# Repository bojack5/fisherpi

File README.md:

# FisherPi
Python code for controlling robo TX Automation Robots via raspberry pi

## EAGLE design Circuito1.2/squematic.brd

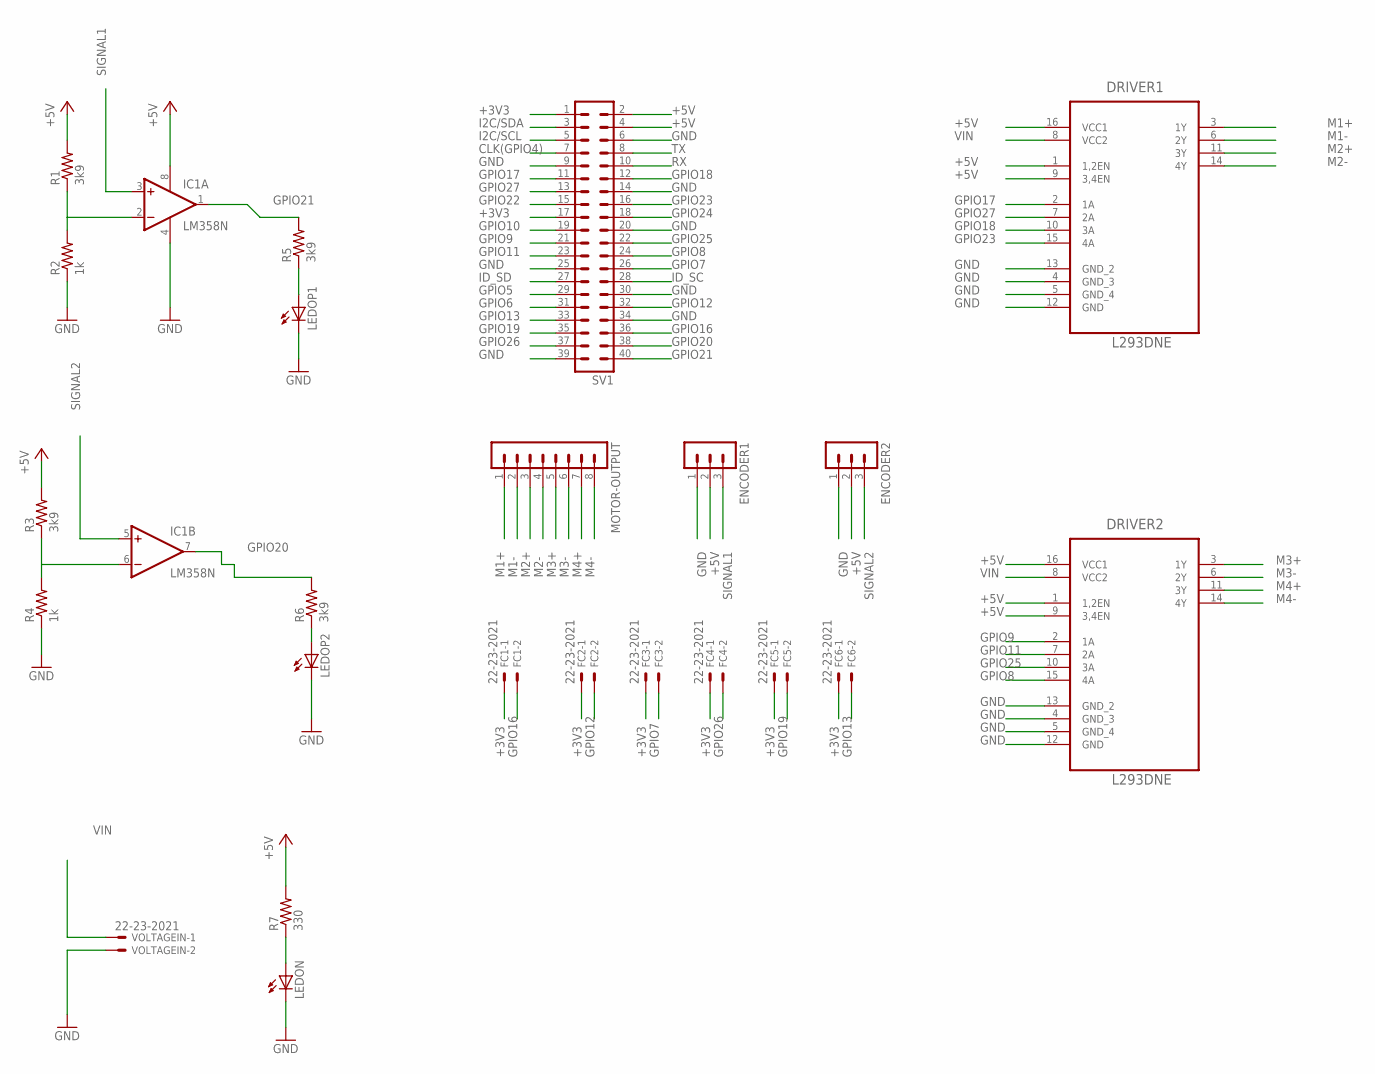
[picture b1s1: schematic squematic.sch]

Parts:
DRIVER1, DRIVER2: L293DNE; DIP254P762X508-16
ENCODER1, ENCODER2: MA03-1
FC1, FC2, FC3, FC4, FC5, FC6: 22-23-2021
IC1: LM358N; DIL08
LEDON: LED_ELD260; LED_LD260
LEDOP1, LEDOP2: LED_ELD260; LED_LD260
MOTOR-OUTPUT: MA08-1
R1, R3, R5, R6: 3k9; 0207/10
R2, R4: 1k; 0207/10
R7: 330; 0207/10
SV1: MA20-2
VOLTAGEIN: 22-23-2021

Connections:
+3V3: FC1.1, FC2.1, FC3.1, FC4.1, FC5.1, FC6.1, SV1.1, SV1.17
+5V: DRIVER1.1 (1,2EN), DRIVER1.9 (3,4EN), DRIVER1.16 (VCC1), DRIVER2.1 (1,2EN), DRIVER2.9 (3,4EN), DRIVER2.16 (VCC1), ENCODER1.2, ENCODER2.2, IC1.8 (V+), R1.2, R3.2, R7.2, SV1.2, SV1.4
CLK(GPIO4): SV1.7
GND: DRIVER1.4 (GND_3), DRIVER1.5 (GND_4), DRIVER1.12 (GND), DRIVER1.13 (GND_2), DRIVER2.4 (GND_3), DRIVER2.5 (GND_4), DRIVER2.12 (GND), DRIVER2.13 (GND_2), ENCODER1.1, ENCODER2.1, IC1.4 (V-), LEDON.K (C), LEDOP1.K (C), LEDOP2.K (C), R2.1, R4.1, SV1.6, SV1.9, SV1.14, SV1.20, SV1.25, SV1.30, SV1.34, SV1.39, VOLTAGEIN.2
GPIO5: SV1.29
GPIO6: SV1.31
GPIO7: FC3.2, SV1.26
GPIO8: DRIVER2.15 (4A), SV1.24
GPIO9: DRIVER2.2 (1A), SV1.21
GPIO10: SV1.19
GPIO11: DRIVER2.7 (2A), SV1.23
GPIO12: FC2.2, SV1.32
GPIO13: FC6.2, SV1.33
GPIO16: FC1.2, SV1.36
GPIO17: DRIVER1.2 (1A), SV1.11
GPIO18: DRIVER1.10 (3A), SV1.12
GPIO19: FC5.2, SV1.35
GPIO20: IC1.7 (OUT), R6.2, SV1.38
GPIO21: IC1.1 (OUT), R5.2, SV1.40
GPIO22: SV1.15
GPIO23: DRIVER1.15 (4A), SV1.16
GPIO24: SV1.18
GPIO25: DRIVER2.10 (3A), SV1.22
GPIO26: FC4.2, SV1.37
GPIO27: DRIVER1.7 (2A), SV1.13
I2C/SCL: SV1.5
I2C/SDA: SV1.3
ID_SC: SV1.28
ID_SD: SV1.27
M1+: DRIVER1.3 (1Y), MOTOR-OUTPUT.1
M1-: DRIVER1.6 (2Y), MOTOR-OUTPUT.2
M2+: DRIVER1.11 (3Y), MOTOR-OUTPUT.3
M2-: DRIVER1.14 (4Y), MOTOR-OUTPUT.4
M3+: DRIVER2.3 (1Y), MOTOR-OUTPUT.5
M3-: DRIVER2.6 (2Y), MOTOR-OUTPUT.6
M4+: DRIVER2.11 (3Y), MOTOR-OUTPUT.7
M4-: DRIVER2.14 (4Y), MOTOR-OUTPUT.8
unnamed: IC1.2 (-IN), R1.1, R2.2
unnamed: IC1.6 (-IN), R3.1, R4.2
unnamed: LEDOP1.A, R5.1
unnamed: LEDOP2.A, R6.1
unnamed: LEDON.A, R7.1
RX: SV1.10
SIGNAL1: ENCODER1.3, IC1.3 (+IN)
SIGNAL2: ENCODER2.3, IC1.5 (+IN)
TX: SV1.8
VIN: DRIVER1.8 (VCC2), DRIVER2.8 (VCC2), VOLTAGEIN.1

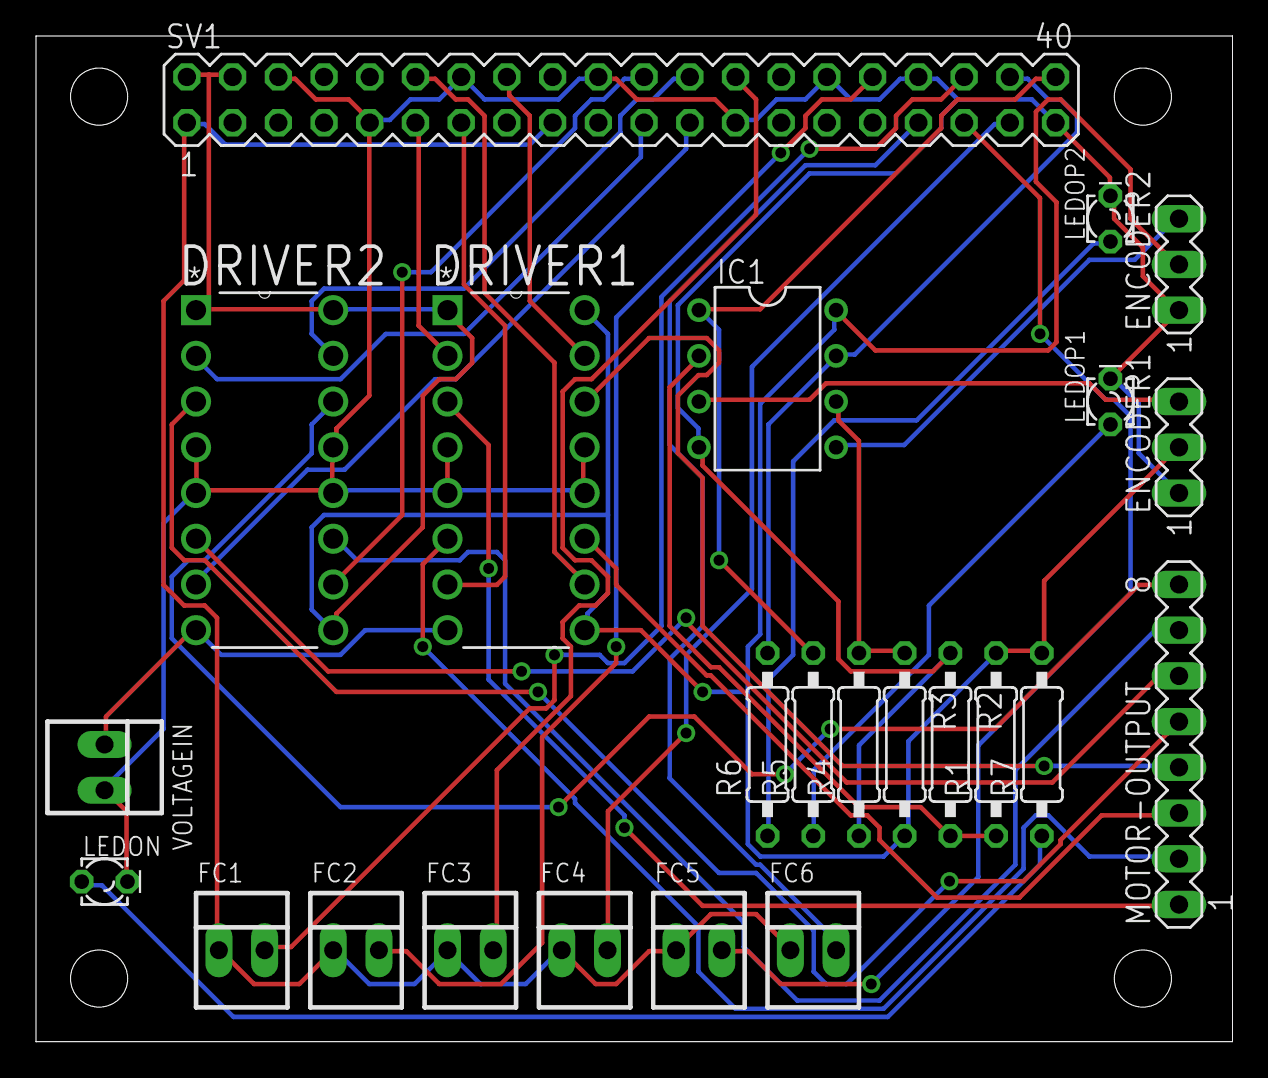
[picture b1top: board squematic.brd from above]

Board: 2 copper layers, 66.5 x 55.9 mm, 24 parts (0 on the bottom side), 35 nets.

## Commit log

2016-05-30 Estructura basica de codigo , y primer commit
2016-05-30 Estructura basica de codigo , y p
2016-05-30 estructura codigo de encoders e interrupciones
2016-05-30 Interrupciones para encoder usando pigpio
2016-05-31 Programa de motor con decicion decision de direccion a partir de velocidad , y la velocidad decidida por medio de PWM con un programa en C
2016-05-31 Programacion y acomode de estructura de PID de posicion [PID posicion 1.0]
2016-05-31 Checar medidas
    Imprimir una hoja del PDF y asegurarse de que todas las medidad concuerden con los componentes y el RBPi
2016-06-14 Reacomodo de Gerbers PCB en Carpeta
2016-07-25 Pines de board como diccionario
2016-07-29 PCB 1.1
2016-07-29 PCB Version 2.1
2016-07-30 PCB Fischer FINAL Subido a PCBWAY
2016-07-31 Agregado de layer drill
2016-08-06 PCB mandados a PCBway
2016-08-16 Libreria de clases de motores , encoders , y Fines de carrera v1.0
2016-08-16 PID posicion 1.0
2016-08-17 Interfaz grafica integrada con PID , y botones de accion
